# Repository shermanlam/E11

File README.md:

E11
===

##Contact
Sherman Lam
slam@g.hmc.edu / shermanator94@yahoo.com
(626)383-1787

##Overview
This repository is used for storing any data for HMC's E11 course. It is primarily used for keeping track of the the beacon boards used for the competition playing field. The beacons are all designed using Eagle. Included in this repository is a library for custom components.

##Beacon Boards 

###V2

Second generation beacon boards and features uniformity between all types of beacons. All boards have the same code and hardware. This board was used in the 2014 Fall E11 course.

####Features
- All boards are capable of being bumped or flashed to. 
- 1 switch to select between bonus beacon mode vs normal mode
- 1 switch to select between flash vs bump modes
- SPI broken out
- All LEDs on transistor circuits

####Known Issues
- Gold-Code-flashing LEDs are spaced too far apart. Deadband when too close
- Push buttons work but are hard to push and can only be pushed from certain angles
- Current limiting resistors have debatable values. Adjust as needed.
- Gold code flashing LEDs need a current limiting resister per LED. Can't share
- LEDs currently powered off VDD (whatever comes in). Change to regulated 5V
- Board is slightly too long and jams on the playing field.

###V3

Third generation board that uses the 2nd generation board's general layout but fixes the known issues. This board has not been produced.

####Features
- Uses the omron tactile switches (B3F-4050).
- Additional switch to select between starting color.

####Known Issues / TODO
- Change switch for starting color to 3 pos? (green, white, unclaimed).

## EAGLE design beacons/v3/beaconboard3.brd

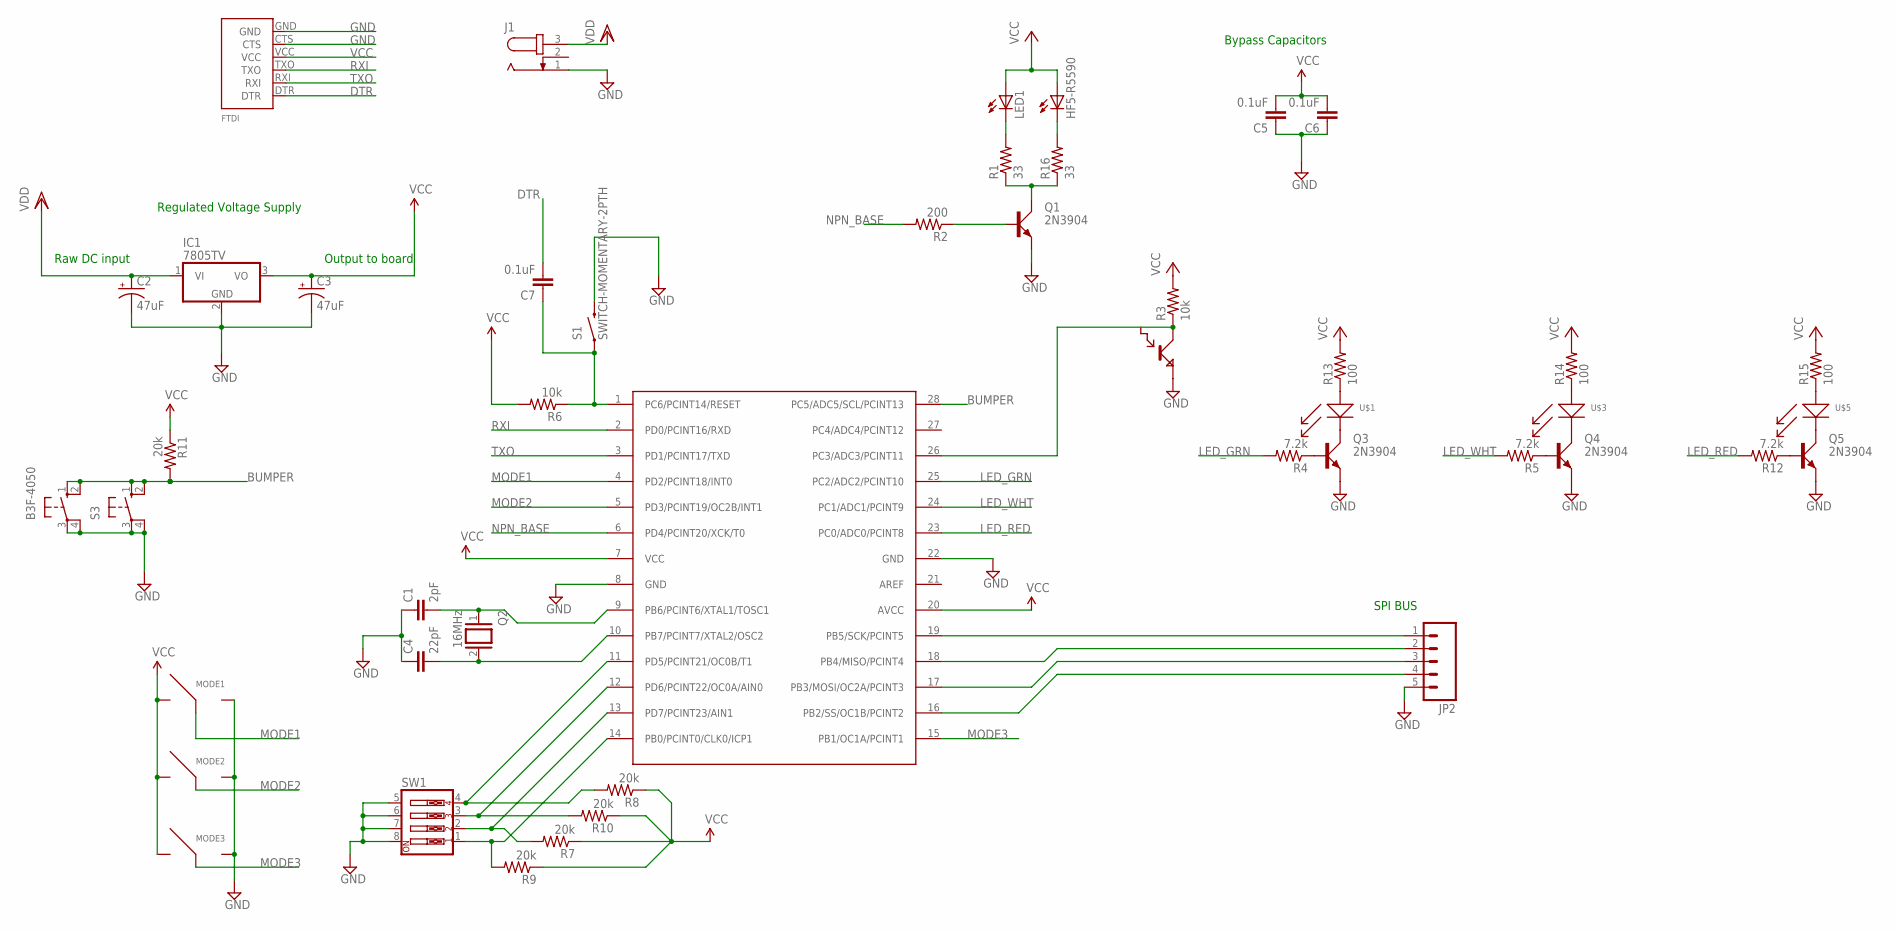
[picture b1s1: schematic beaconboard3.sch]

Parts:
B3F-4050: 40-XX; B3F-40XX
C1: 2pF; CAP-PTH-SMALL
C2, C3: 47uF; CPOL-RADIAL-10UF-25V
C4: 22pF; CAP-PTH-SMALL
C5, C6, C7: 0.1uF; CAP-PTH-5MM
HF5-R5590: LED-2AC-CP41B-WES; CP41B
IC1: 7805TV; TO220V
J1: JACK-PLUG1; SPC4078
JP2: M05LOCK_LONGPADS; 1X05_LOCK_LONGPADS
LED1: LED-2AC-CP41B-WES; CP41B
MODE1, MODE2, MODE3: SPD_SLIDE_SWITCH; SPDT_SLIDE_SWITCH
Q1, Q3, Q4, Q5: 2N3904; TO92D
Q2: 16MHz; QS
R1, R16: 33; AXIAL-0.4
R2: 200; AXIAL-0.4
R3, R6: 10k; AXIAL-0.4
R4, R5, R12: 7.2k; AXIAL-0.4
R7, R8, R9, R10, R11: 20k; AXIAL-0.4
R13, R14, R15: 100; AXIAL-0.4
S1: SWITCH-MOMENTARY-2PTH; TACTILE-PTH
S3: 40-XX; B3F-40XX
SW1: SW_DIP-4; EDG-04
U$1, U$3, U$5: 8MM_LED
U$2: BPW77NA; TO-18
U$4: ATMEGA328; DIL28-3
U$6: FTDI

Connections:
BUMPER: B3F-4050.1 (S), B3F-4050.2 (S1), R11.P$2 (2), S3.1 (S), S3.2 (S1), U$4.28 (PC5/ADC5/SCL/PCINT13)
DTR: C7.2, U$6.DTR
GND: B3F-4050.3, B3F-4050.4 (P1), C1.1, C2.2 (-), C3.2 (-), C4.1, C5.1, C6.1, IC1.2 (GND), J1.1, JP2.5, MODE1.3, MODE2.3, MODE3.3, Q1.E, Q3.E, Q4.E, Q5.E, S1.3 (2), S3.3, S3.4 (P1), SW1.5, SW1.6, SW1.7, SW1.8, U$2.E, U$4.8 (GND), U$4.22 (GND), U$6.CTS, U$6.GND
LED_GRN: R4.P$2 (2), U$4.25 (PC2/ADC2/PCINT10)
LED_RED: R12.P$2 (2), U$4.23 (PC0/ADC0/PCINT8)
LED_WHT: R5.P$2 (2), U$4.24 (PC1/ADC1/PCINT9)
MODE1: MODE1.2, U$4.4 (PD2/PCINT18/INT0)
MODE2: MODE2.2, U$4.5 (PD3/PCINT19/OC2B/INT1)
MODE3: MODE3.2, U$4.15 (PB1/OC1A/PCINT1)
unnamed: Q1.C, R1.P$1 (1), R16.P$1 (1)
unnamed: Q1.B, R2.P$1 (1)
unnamed: LED1.1 (C), LED1.4 (C), R1.P$2 (2)
unnamed: Q3.B, R4.P$1 (1)
unnamed: JP2.1, U$4.19 (PB5/SCK/PCINT5)
unnamed: JP2.2, U$4.18 (PB4/MISO/PCINT4)
unnamed: JP2.3, U$4.17 (PB3/MOSI/OC2A/PCINT3)
unnamed: Q4.B, R5.P$1 (1)
unnamed: R3.P$1 (1), U$2.C, U$4.26 (PC3/ADC3/PCINT11)
unnamed: Q5.B, R12.P$1 (1)
unnamed: C7.1, R6.P$1 (1), S1.1, U$4.1 (PC6/PCINT14/RESET)
unnamed: C1.2, Q2.1, U$4.9 (PB6/PCINT6/XTAL1/TOSC1)
unnamed: C4.2, Q2.2, U$4.10 (PB7/PCINT7/XTAL2/OSC2)
unnamed: R7.P$2 (2), SW1.2, U$4.13 (PD7/PCINT23/AIN1)
unnamed: R8.P$2 (2), SW1.4, U$4.11 (PD5/PCINT21/OC0B/T1)
unnamed: R10.P$2 (2), SW1.3, U$4.12 (PD6/PCINT22/OC0A/AIN0)
unnamed: Q3.C, U$1.NEG
unnamed: Q4.C, U$3.NEG
unnamed: R9.P$2 (2), SW1.1, U$4.14 (PB0/PCINT0/CLK0/ICP1)
unnamed: JP2.4, U$4.16 (PB2/SS/OC1B/PCINT2)
unnamed: Q5.C, U$5.NEG
unnamed: R13.P$1 (1), U$1.POS
unnamed: R14.P$1 (1), U$3.POS
unnamed: R15.P$1 (1), U$5.POS
unnamed: HF5-R5590.1 (C), HF5-R5590.4 (C), R16.P$2 (2)
NPN_BASE: R2.P$2 (2), U$4.6 (PD4/PCINT20/XCK/T0)
RXI: U$4.2 (PD0/PCINT16/RXD), U$6.TXO
TXO: U$4.3 (PD1/PCINT17/TXD), U$6.RXI
VCC: C3.1 (+), C5.2, C6.2, HF5-R5590.2 (A), HF5-R5590.3 (A), IC1.3 (VO), LED1.2 (A), LED1.3 (A), MODE1.1, MODE2.1, MODE3.1, R3.P$2 (2), R6.P$2 (2), R7.P$1 (1), R8.P$1 (1), R9.P$1 (1), R10.P$1 (1), R11.P$1 (1), R13.P$2 (2), R14.P$2 (2), R15.P$2 (2), U$4.7 (VCC), U$4.20 (AVCC), U$6.VCC
VDD: C2.1 (+), IC1.1 (VI), J1.3

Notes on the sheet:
Output to board
Raw DC input
Bypass Capacitors
Regulated Voltage Supply
SPI BUS

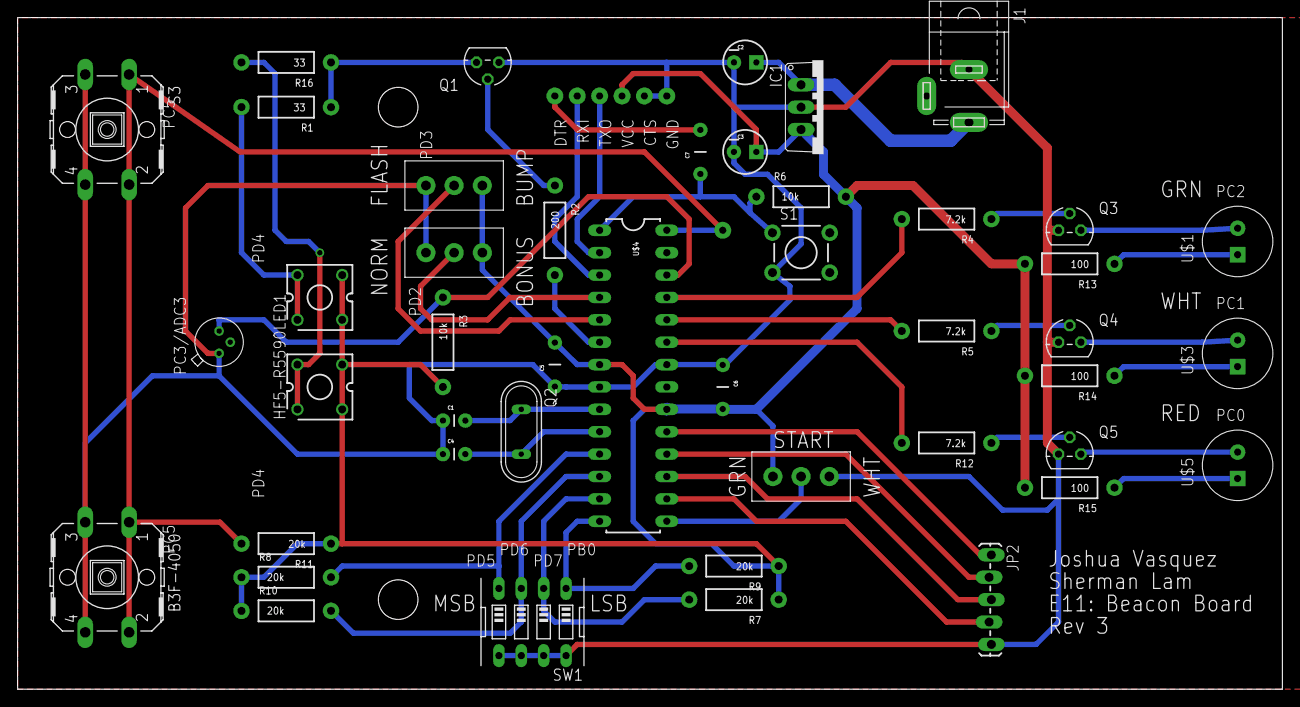
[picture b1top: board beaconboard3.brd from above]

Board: 2 copper layers, 143.5 x 76.2 mm, 46 parts (0 on the bottom side), 39 nets.

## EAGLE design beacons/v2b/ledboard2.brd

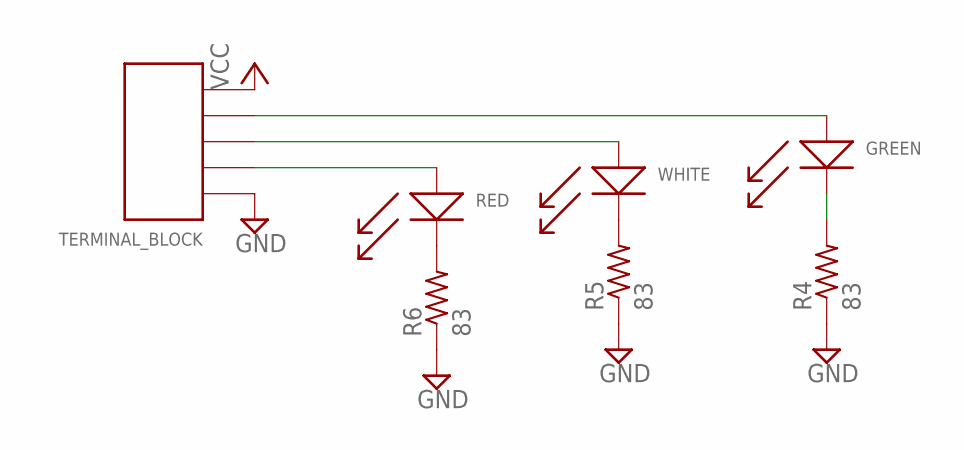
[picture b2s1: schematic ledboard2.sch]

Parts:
GREEN: 8MM_LED
R4, R5, R6: 83; 0207/12
RED: 8MM_LED
TERMINAL_BLOCK: 1X5_3.5MM_TERMINAL_BLOCK
WHITE: 8MM_LED

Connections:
GND: R4.1, R5.1, R6.1, TERMINAL_BLOCK.5
unnamed: RED.POS, TERMINAL_BLOCK.4
unnamed: TERMINAL_BLOCK.3, WHITE.POS
unnamed: GREEN.POS, TERMINAL_BLOCK.2
unnamed: GREEN.NEG, R4.2
unnamed: R5.2, WHITE.NEG
unnamed: R6.2, RED.NEG
VCC: TERMINAL_BLOCK.1

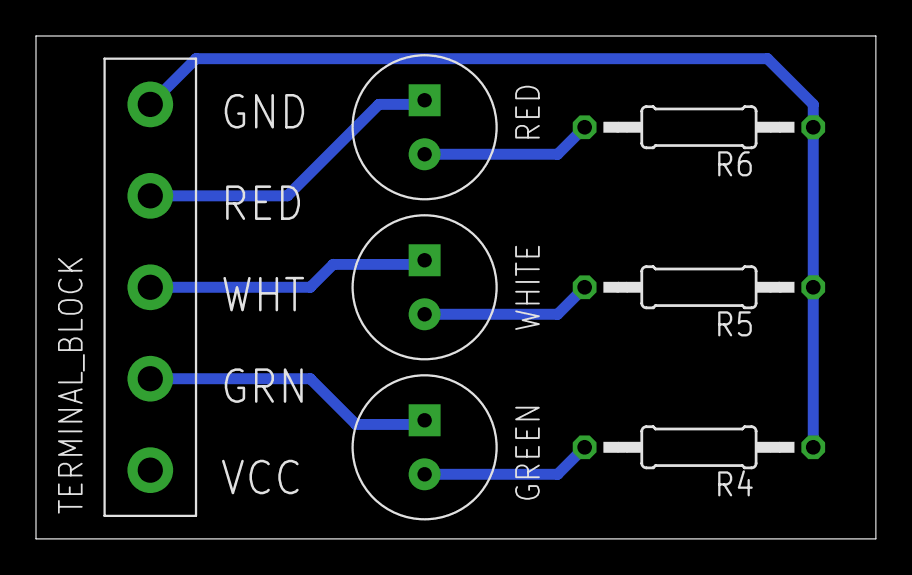
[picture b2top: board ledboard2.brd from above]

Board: 2 copper layers, 46.7 x 27.9 mm, 7 parts (0 on the bottom side), 7 nets.

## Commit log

2014-09-23 Added E11 board
2014-09-27 Added LED breakout board and e11 eagle library
2014-09-28 Added phototransistor
2014-09-30 Added switches for mode control
2014-10-09 Added beaconboard 3, extended version
2014-11-05 Updated beaconboard with staff suggestions
2014-11-21 Restructured the directory
2014-11-21 Restructure directory
2014-11-23 Fixed headers on the readme
2014-11-23 Adjusted headers agagin
2014-12-03 Updated readme. Added omron switches in version 3
2014-12-03 Added pdf of sch and updated boms

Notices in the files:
parts and their libraries:
SparkFun-Capacitors: Licensing: CC v3.0 Share-Alike You are welcome to use this library for commercial purposes.
